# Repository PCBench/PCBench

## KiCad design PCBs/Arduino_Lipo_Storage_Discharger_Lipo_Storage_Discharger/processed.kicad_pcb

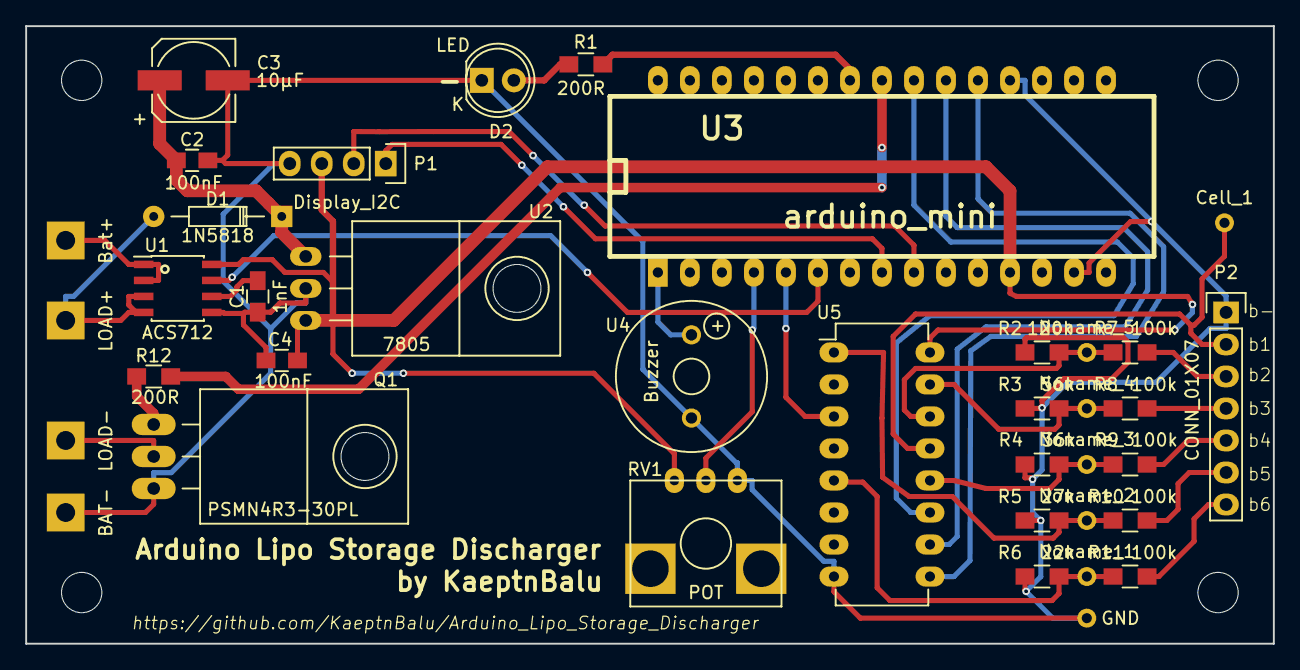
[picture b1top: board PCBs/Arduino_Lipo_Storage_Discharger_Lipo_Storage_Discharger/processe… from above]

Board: 2 copper layers, 99.0 x 49.0 mm, 38 parts (0 on the bottom side), 31 nets.

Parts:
C1: 1nF; C_0805_HandSoldering
C2, C4: 100nF; C_0805_HandSoldering
C3: 10µF; c_elec_6.3x5.3
Cell_1: T1; Measurement_Point_Round-TH_Small
D1: 1N5818; Diode_DO-35_SOD27_Horizontal_RM10
D2: LED; LED-5MM
Noname_1, Noname_2, Noname_3, Noname_4, Noname_5: Measurement_Point_Round-TH_Small
P1: Display_I2C; Socket_Strip_Straight_1x04
P2: CONN_01X07; Pin_Header_Straight_1x07
Q1: PSMN4R3-30PL; TO-220_Neutral123_Horizontal_LargePads
R1, R12: 200R; R_0805_HandSoldering
R2: 120k; R_0805_HandSoldering
R3: 56k; R_0805_HandSoldering
R4: 36k; R_0805_HandSoldering
R5: 27k; R_0805_HandSoldering
R6: 22k; R_0805_HandSoldering
R7, R8, R9, R10, R11: 100k; R_0805_HandSoldering
RV1: POT; RK09K1130A5R
U1: ACS712; SOIC-8_3.9x4.9mm_Pitch1.27mm
U2: 7805; TO-220_7805_Horizontal
U3: arduino_mini
U4: Buzzer; Buzzer_12x8.2_RM6.6
U5: 4051; DIP-16_W7.62mm_LongPads
W1: LOAD+; Measurement_Point_Square-TH_Big
W2: Bat+; Measurement_Point_Square-TH_Big
W3: LOAD-; Measurement_Point_Square-TH_Big
W4: BAT-; Measurement_Point_Square-TH_Big
W5: GND; Measurement_Point_Round-TH_Small

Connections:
/Cell_1: Cell_1.1, P2.2, U5.13
/Cell_2: Noname_5.1, R2.1, R7.2, U5.14
/Cell_3: Noname_4.1, R3.1, R8.2, U5.15
/Cell_4: Noname_3.1, R4.1, R9.2, U5.12
/Cell_5: Noname_2.1, R5.1, R10.2, U5.1
/Cell_6: Noname_1.1, R6.1, R11.2, U5.5
A1: U3.5, U5.3
A2: U1.7, U3.6
Bat+: U1.1, U1.2, W2.1
Bat-: C1.1, C2.2, C3.2, C4.2, D2.1, P1.4, P2.1, Q1.3, R2.2, R3.2, R4.2, R5.2, R6.2, RV1.1, U1.5, U2.GND, U3.14, U3.19, U4.2, U5.8, W4.1, W5.1
D2: U3.20, U5.9
D3: U3.21, U5.10
D4: U3.22, U5.11
D6: R1.2, U3.24
D13: U3.1, U4.1
Input+: D1.2, U1.3, U1.4, W1.1
LOAD-: Q1.2, W3.1
unnamed: C1.2, U1.6
unnamed: C2.1, C3.1, D1.1, U2.VI
unnamed: D2.2, R1.1
unnamed: P2.3, R7.1
unnamed: P2.4, R8.1
unnamed: P2.5, R9.1
unnamed: P2.6, R10.1
unnamed: P2.7, R11.1
unnamed: Q1.1, R12.2
unnamed: R12.1, U3.23
unnamed: RV1.2, U3.4
SCL: P1.2, U3.9
SDA: P1.1, U3.8
VCC: C4.1, P1.3, RV1.3, U1.8, U2.VO, U3.12, U5.16

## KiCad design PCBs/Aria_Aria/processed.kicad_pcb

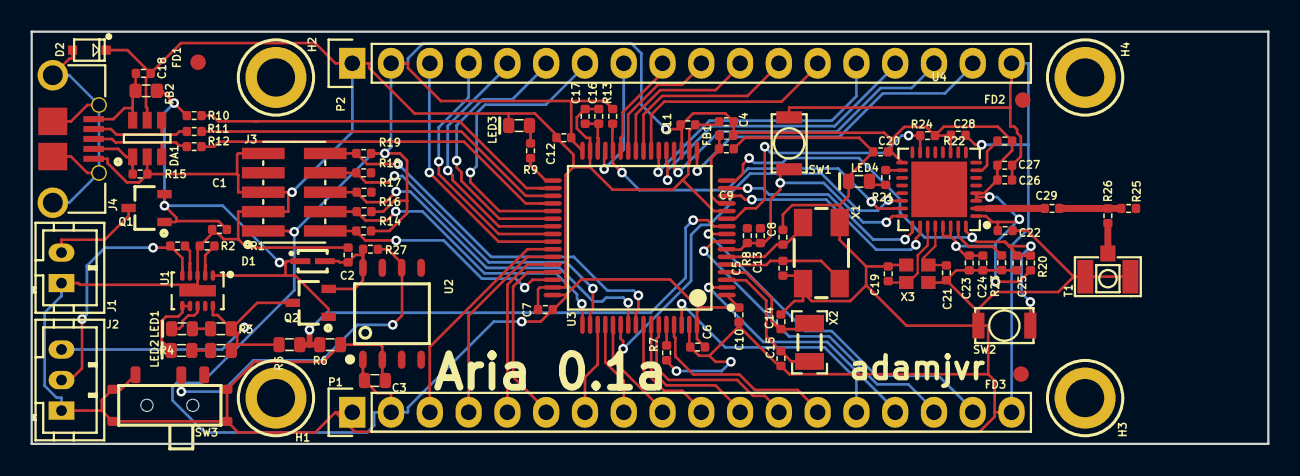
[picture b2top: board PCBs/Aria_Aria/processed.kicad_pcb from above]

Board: 4 copper layers, 81.0 x 27.0 mm, 91 parts (0 on the bottom side), 83 nets.

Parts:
C1, C2: CL05A105KA5NQNC; C0402
C3: CL10A106KQ8NNNC; C0603
C4, C6, C7, C9, C10, C11, C12, C13, C17, C18, C20, C22, C23, C24, C25, C26, C27, C28: CL05B104JP5NNNC; C0402
C5, C8, C19, C21: CL05C090CB5NNNC; C0402
C14, C15: CL05C180GB5NCNC; C0402
C16: CL05A475KQ5NRNC; C0402
C29: 600L5R6BT200T; C0402
D1: BAT20JFILM
D2: RSB39VTE-17
DA1: ESDA6V1BC6
FB1: BLM15HG601SN1D
FB2: MI0603K300R-10
FD1, FD2, FD3: FIDUCIAL
H1, H2, H3, H4: M2.5_Hole; M2.5_HOLE
J1: B2B-PH-K-S(LF)(SN)
J2: B3B-PH-K-S(LF)(SN)
J3: 20021121-00010C4LF
J4: 0475890001-MicroUSBPort; 0475890001
LED1: LTST-C191KGKT; LED0603
LED2: LTST-C191KFKT; LED0603
LED3, LED4: LTST-C193TBKT-5A; LED0603
P1, P2: CONN_01X18; Socket_Strip_Straight_1x18
Q1, Q2: DMG2307L-7
R1: RC1005F4870CS; R0402
R2, R8, R9, R14, R16, R17, R18, R19, R20, R21: RC1005F102CS; R0402
R3, R4: RC1608J202CS; R0603
R5, R6: ERA-3AEB3741V; R0603
R7, R10, R13, R24, R27: RC1005F103CS; R0402
R11, R12: CPF0402B22RE1; R0402
R15: RC1005J473CS; R0402
R22, R23: RC1005F123CS; R0402
R25, R26: ERJ-2GE0R00X; R0402
SW1, SW2: B3U-1000P
SW3: CUS-12TB
T1: 1909763-1
U1: BQ24210DQCT; BQ24210
U2: TC1265-3.3VOA
U3: STM32F446RET6_-_TQFP64; STM32F446RET6
U4: ESP8285
X1: ABM3B8.000MHZB2T
X2: ABS07-32.768KHZ-9-T
X3: FA-128_26.0000MF10Z-AC3

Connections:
+3V3: C3.1, C4.1, C6.1, C7.1, C10.1, C11.1, C12.1, C20.1, C22.1, C23.1, C24.1, C26.1, C27.1, C28.1, FB1.1, J3.1, P1.2, P2.2, R13.1, R14.1, R16.1, R19.1, R20.2, R22.2, R24.1, U2.1, U3.1, U3.19, U3.32, U3.48, U3.64, U4.1, U4.3, U4.4, U4.11, U4.17, U4.29, U4.30
/MCU_STM32F446RET6/BAT_VOLT: R5.2, R6.1, U3.10
/MCU_STM32F446RET6/ESPTOST_BOOT0: U3.54, U4.22
/MCU_STM32F446RET6/ESPTOST_BOOT1: R13.2, U3.28, U4.23
/MCU_STM32F446RET6/ESP_PGM_MODE: R24.2, U3.11, U4.15
/MCU_STM32F446RET6/ESP_ST_RST: C13.1, R8.2, SW1.1, U3.7, U4.24
/MCU_STM32F446RET6/ESP_URX: U3.14, U4.26
/MCU_STM32F446RET6/ESP_UTX: U3.15, U4.25
/MCU_STM32F446RET6/HEARTBEAT: R9.1, U3.33
/MCU_STM32F446RET6/NJTRST: J3.10, R19.2, U3.56
/MCU_STM32F446RET6/PA3: P2.17, U3.17
/MCU_STM32F446RET6/PA4: P2.16, U3.20
/MCU_STM32F446RET6/PA5: P2.15, U3.21
/MCU_STM32F446RET6/PA6: P2.14, U3.22
/MCU_STM32F446RET6/PA7: P2.13, U3.23
/MCU_STM32F446RET6/PA8: P2.3, U3.41
/MCU_STM32F446RET6/PA9: P1.3, U3.42
/MCU_STM32F446RET6/PA10: P1.4, U3.43
/MCU_STM32F446RET6/PA11: P1.5, U3.44
/MCU_STM32F446RET6/PA12: P1.6, U3.45
/MCU_STM32F446RET6/PB0: P2.10, U3.26
/MCU_STM32F446RET6/PB1: P2.9, U3.27
/MCU_STM32F446RET6/PB5: P1.10, U3.57
/MCU_STM32F446RET6/PB6: P1.11, U3.58
/MCU_STM32F446RET6/PB7: P1.12, U3.59
/MCU_STM32F446RET6/PB8: P1.13, U3.61
/MCU_STM32F446RET6/PB9: P1.14, U3.62
/MCU_STM32F446RET6/PB10: P2.8, U3.29
/MCU_STM32F446RET6/PC0: P1.16, U3.8
/MCU_STM32F446RET6/PC1: P1.17, U3.9
/MCU_STM32F446RET6/PC4: P2.12, U3.24
/MCU_STM32F446RET6/PC5: P2.11, U3.25
/MCU_STM32F446RET6/PC6: P2.7, U3.37
/MCU_STM32F446RET6/PC7: P2.6, U3.38
/MCU_STM32F446RET6/PC8: P2.5, U3.39
/MCU_STM32F446RET6/PC9: P2.4, U3.40
/MCU_STM32F446RET6/PC10: P1.7, U3.51
/MCU_STM32F446RET6/PC11: P1.8, U3.52
/MCU_STM32F446RET6/PC12: P1.9, U3.53
/MCU_STM32F446RET6/PC13: P1.15, U3.2
/MCU_STM32F446RET6/STM_ESP_RST: C25.1, R20.1, SW2.2, U3.16, U4.32
/MCU_STM32F446RET6/SWCLK_TCK: J3.4, R16.2, U3.49
/MCU_STM32F446RET6/SWDIO_TMS: J3.2, R14.2, U3.46
/MCU_STM32F446RET6/SWO_TDI: J3.8, R18.2, U3.50
/MCU_STM32F446RET6/SWO_TDO: J3.6, R17.2, U3.55
/MCU_STM32F446RET6/VBUS: C1.1, D1.1, FB2.1, Q1.1, Q1.2, Q2.1, R10.2, U1.1
/Power/BAT: J2.3, Q2.3, R3.2, R4.2, R5.1, U1.10
/Power/LDO_VIN: C2.1, D1.2, Q2.2, R27.1, U2.8
/Power/THERM: J2.2, R2.2, U1.5
/WiFi-ESP8285/ANTENNA: C29.2, R25.1, R26.1
/WiFi-ESP8285/ANT_UM: R26.2, T1.1
/WiFi-ESP8285/LNA: C29.1, U4.2
GND: C1.2, C2.2, C3.2, C4.2, C5.2, C6.2, C7.2, C8.2, C9.2, C10.2, C11.2, C12.2, C14.2, C15.2, C16.2, C17.2, C18.1, C19.2, C20.2, C21.2, C22.2, C23.2, C24.2, C25.2, C26.2, C27.2, C28.2, D2.2, DA1.2, DA1.5, J1.1, J2.1, J3.3, J3.5, J3.9, J4.5, LED3.2, LED4.2, P1.1, P1.18, P2.1, P2.18, R1.2, R6.2, R7.2, R15.2, R23.1, SW1.2, SW2.1, SW3.1, SW3.4, T1.2, U1.3, U1.11, U2.2, U3.12, U3.18, U3.31, U3.47, U3.63, X1.2, X1.4, X3.2, X3.4
unnamed: C5.1, U3.5, X1.1
unnamed: C8.1, U3.6, X1.3
unnamed: C9.1, FB1.2, U3.13
unnamed: C14.1, U3.4, X2.1
unnamed: C15.1, U3.3, X2.2
unnamed: C16.1, C17.1, U3.30
unnamed: C18.2, DA1.6, FB2.2, J4.1
unnamed: C19.1, U4.27, X3.1
unnamed: C21.1, U4.28, X3.3
unnamed: D2.1, J4.6, J4.7, J4.8, J4.9, J4.10, J4.11
unnamed: DA1.1, J4.4, R15.1
unnamed: DA1.3, J4.3, R12.2
unnamed: DA1.4, J4.2, R11.2
unnamed: J1.2, Q1.3
unnamed: LED1.1, R3.1
unnamed: LED1.2, U1.8
unnamed: LED2.1, R4.1
unnamed: LED2.2, U1.6, U1.7
unnamed: LED3.1, R9.2
unnamed: LED4.1, R21.2
unnamed: R1.1, U1.2
unnamed: R2.1, U1.4
unnamed: R7.1, U3.60
unnamed: R10.1, U3.34
unnamed: R11.1, U3.35
unnamed: R12.1, U3.36
unnamed: R21.1, U4.18
unnamed: R22.1, U4.7
unnamed: R23.2, U4.31
unnamed: R27.2, SW3.2, U2.6

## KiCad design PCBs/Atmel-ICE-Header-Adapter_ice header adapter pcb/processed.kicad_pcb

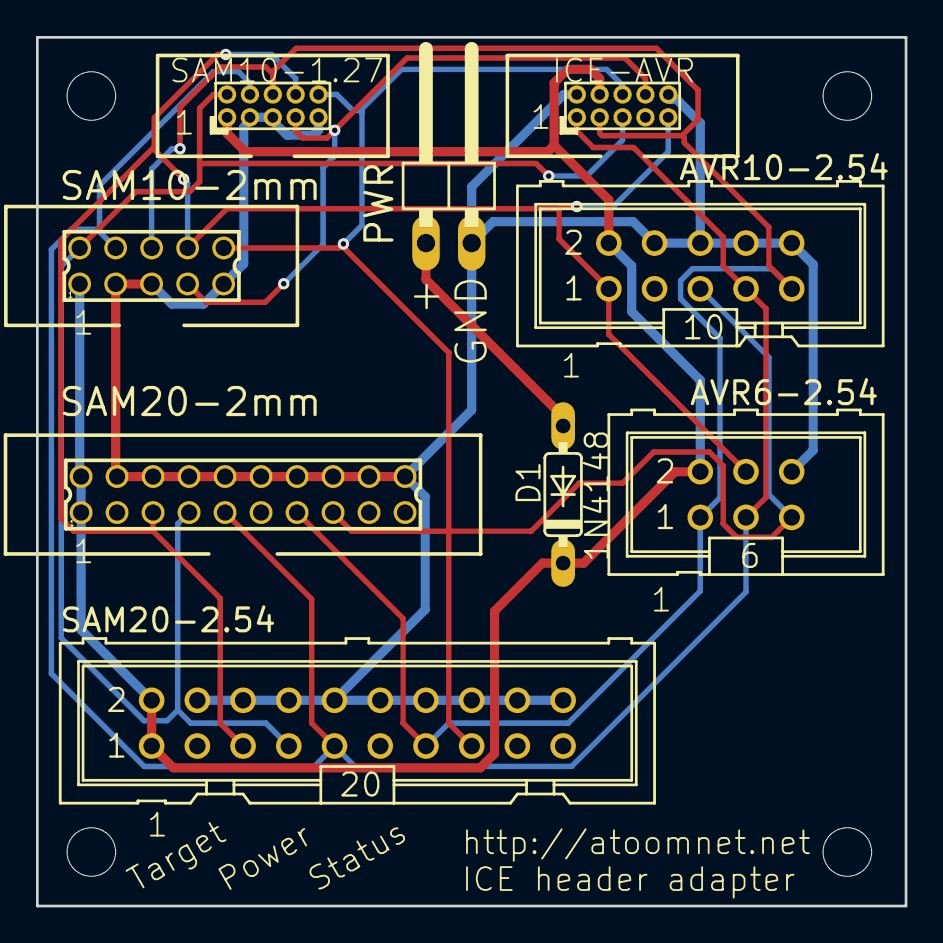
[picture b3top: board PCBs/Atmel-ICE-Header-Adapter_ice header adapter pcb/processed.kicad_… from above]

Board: 2 copper layers, 48.3 x 48.3 mm, 13 parts (0 on the bottom side), 9 nets.

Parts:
AVR6-2.54: ML6
AVR10-2.54: ML10
D1: 1N4148; DO35-7
ICE-AVR1: PINHEAD_PINHD-2X5; PINHEAD_2X05_127
P1, P2, P3, P4: TST; MountingHole_2.7mm_M2.5
PWR1: PINHD-1X2; 1X02_90
SAM10-1.27: PINHEAD_PINHD-2X5; PINHEAD_2X05_127
SAM10-2: 87758-1016
SAM20-2: 87758-2016
SAM20-2.54: ML20

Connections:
/GND: AVR6-2.54.6, AVR10-2.54.4, AVR10-2.54.6, AVR10-2.54.8, AVR10-2.54.10, ICE-AVR1.2, ICE-AVR1.10, PWR1.2, SAM10-1.27.3, SAM10-1.27.5, SAM10-1.27.9, SAM10-2.3, SAM10-2.5, SAM10-2.9, SAM20-2.4, SAM20-2.6, SAM20-2.8, SAM20-2.10, SAM20-2.12, SAM20-2.14, SAM20-2.16, SAM20-2.18, SAM20-2.20, SAM20-2.54.4, SAM20-2.54.6, SAM20-2.54.8, SAM20-2.54.10, SAM20-2.54.12, SAM20-2.54.14, SAM20-2.54.16, SAM20-2.54.18, SAM20-2.54.20
/NSRST: AVR6-2.54.5, AVR10-2.54.5, ICE-AVR1.6, SAM10-1.27.10, SAM10-2.10, SAM20-2.15, SAM20-2.54.15
/NTRST: ICE-AVR1.8, SAM10-1.27.7, SAM10-2.7
/TCK: AVR6-2.54.3, AVR10-2.54.7, ICE-AVR1.1, SAM10-1.27.4, SAM10-2.4, SAM20-2.9, SAM20-2.54.9
/TDI: AVR6-2.54.4, AVR10-2.54.1, ICE-AVR1.9, SAM10-1.27.8, SAM10-2.8, SAM20-2.5, SAM20-2.54.5
/TDO: AVR6-2.54.1, AVR10-2.54.9, ICE-AVR1.3, SAM10-1.27.6, SAM10-2.6, SAM20-2.13, SAM20-2.54.13
/TMS: ICE-AVR1.5, SAM10-1.27.2, SAM10-2.2, SAM20-2.7, SAM20-2.54.7
/VTG: AVR6-2.54.2, AVR10-2.54.2, D1.C, ICE-AVR1.4, SAM10-1.27.1, SAM10-2.1, SAM20-2.1, SAM20-2.2, SAM20-2.54.1, SAM20-2.54.2
unnamed: D1.A, PWR1.1

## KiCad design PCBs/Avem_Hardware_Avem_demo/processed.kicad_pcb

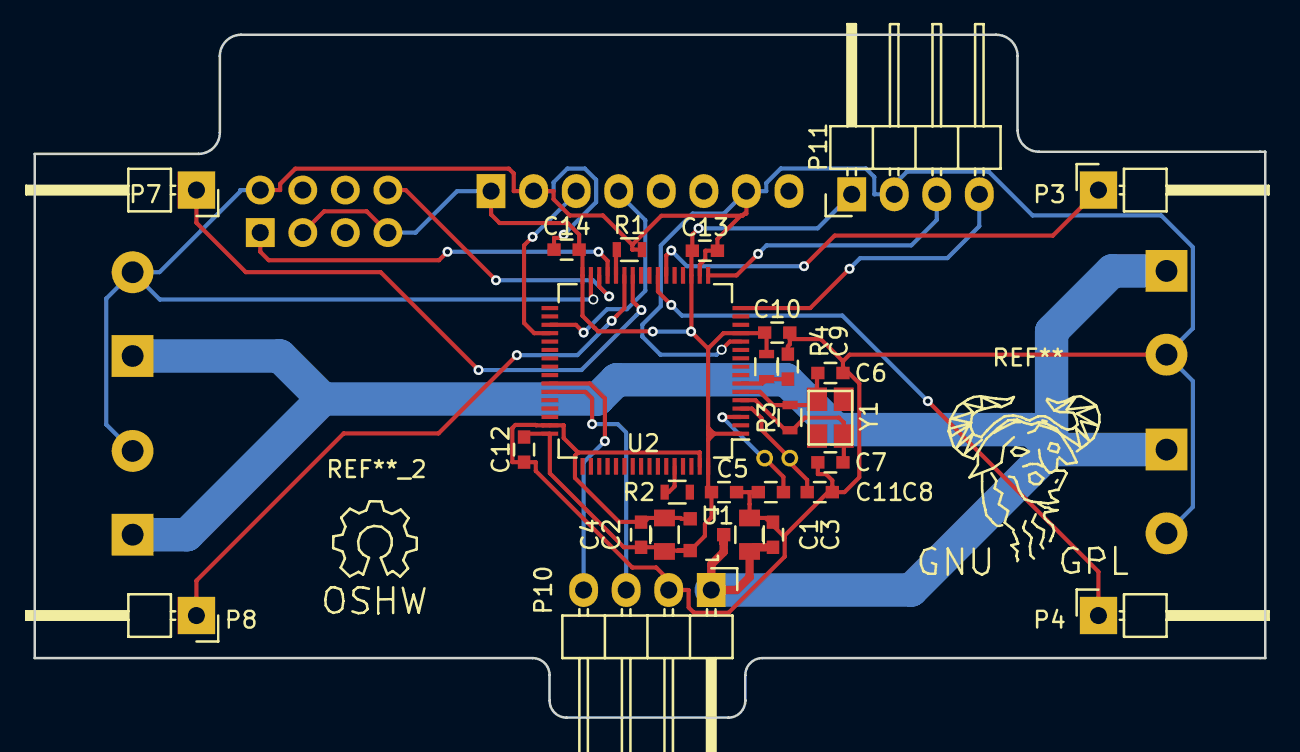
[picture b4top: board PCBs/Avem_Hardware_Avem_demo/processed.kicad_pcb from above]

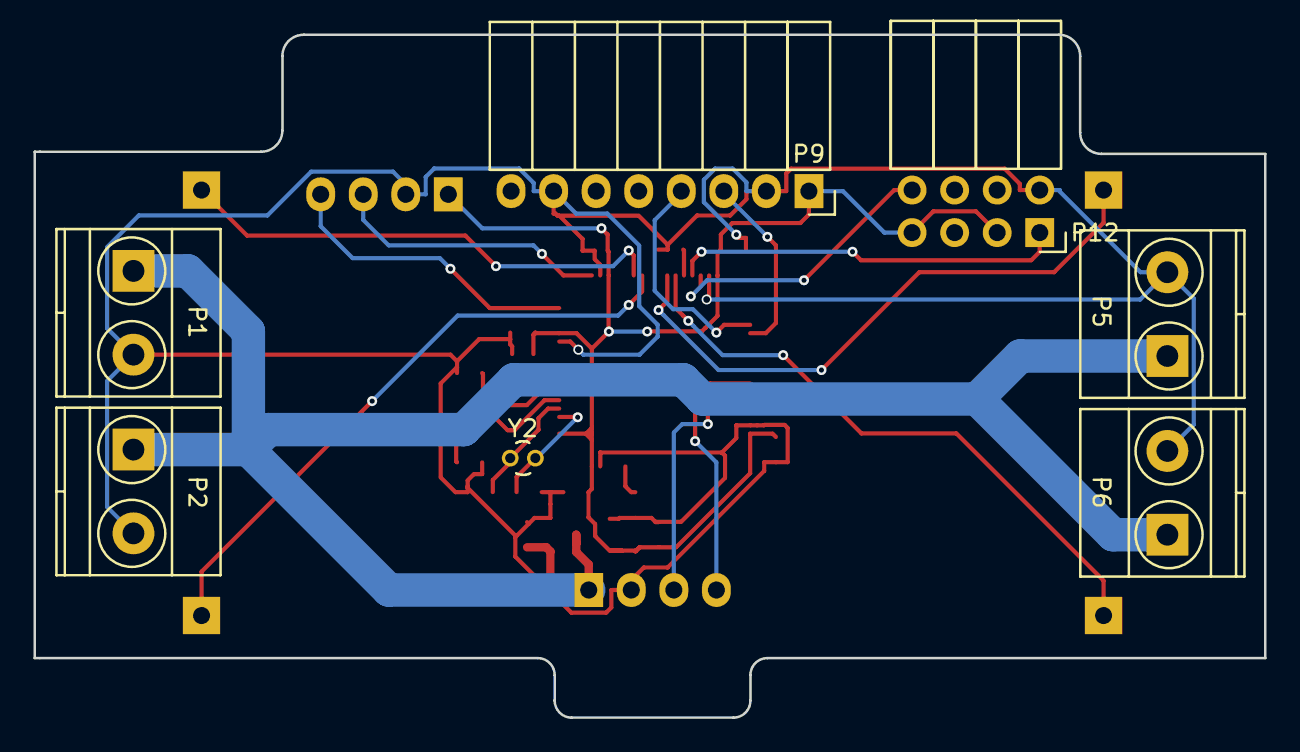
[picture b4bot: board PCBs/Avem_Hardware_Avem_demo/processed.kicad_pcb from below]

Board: 2 copper layers, 73.5 x 40.8 mm, 34 parts (7 on the bottom side), 22 nets.

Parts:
C1, C2: C_0805
C3, C4, C5, C6, C7, C8, C9, C10, C11, C12, C13, C14: C_0603
P1, P2, P5, P6: TerminalBlock_Pheonix_MKDS1.5-2pol
P3, P4, P7, P8: Pin_Header_Angled_1x01
P9: Socket_Strip_Angled_1x08
P10: ISP; Pin_Header_Angled_1x04
P11: Pin_Header_Angled_1x04
P12: Socket_Strip_Angled_2x04
R1, R2, R3, R4: R_0603
U1: SOT-23
U2: STM32F103RCT6; LQFP-64_10x10mm_Pitch0.5mm
Y1: crystal_FA238-TSX3225
Y2: Crystal_Round_Vertical_2mm

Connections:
3V3: C2.1, C4.2, C5.1, C10.1, C12.1, C13.1, C14.1, P9.1, P11.1, P12.3, P12.7, R4.1, U1.2, U2.1, U2.13, U2.19, U2.32, U2.48, U2.64
+3V3: C1.1, C3.2, P1.1, P2.1, P5.1, P6.1, P10.1, U1.3
BLDC1: P3.1, U2.22
BLDC2: P4.1, U2.23
BLDC3: P7.1, U2.26
BLDC4: P8.1, U2.27
BOOT0: R2.2, U2.60
BOOT1: R1.2, U2.28
GND: C1.2, C2.2, C3.1, C4.1, C5.2, C6.2, C7.2, C8.2, C9.2, C10.2, C11.2, C12.2, C13.2, C14.2, P1.2, P2.2, P5.2, P6.2, P9.2, P9.7, P10.2, P11.2, P12.2, R1.1, U1.1, U2.12, U2.18, U2.31, U2.47, U2.63
OSCIN: C7.1, R3.2, U2.5, Y1.2
OSCIN32: C11.1, U2.3, Y2.2
OSCOUT: C6.1, R3.1, U2.6, Y1.1
OSCOUT32: C8.1, U2.4, Y2.1
RESET: C9.1, R4.2, U2.7
RX1: P10.3, U2.43
RX2: P11.3, U2.17
RX3: P12.8, U2.30
SCL: P9.3, U2.36
SDA: P9.4, U2.35
TX1: P10.4, U2.42
TX2: P11.4, U2.16
TX3: P12.1, U2.29

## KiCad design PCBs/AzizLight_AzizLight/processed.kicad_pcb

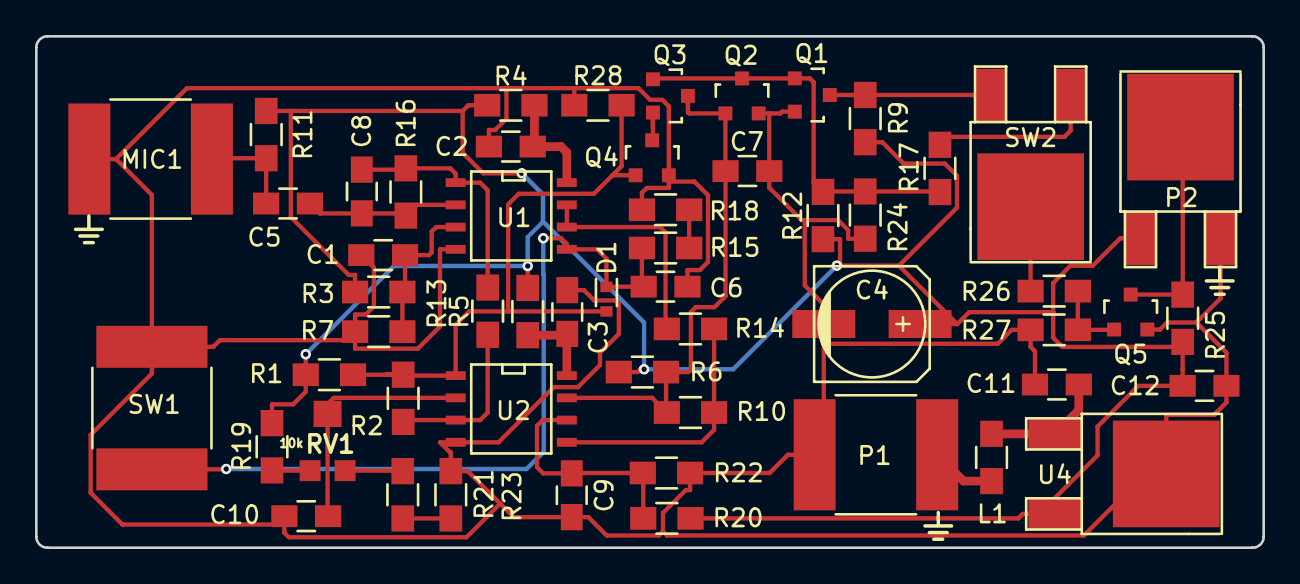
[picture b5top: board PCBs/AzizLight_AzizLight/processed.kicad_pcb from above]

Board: 2 copper layers, 70.1 x 29.2 mm, 55 parts (0 on the bottom side), 29 nets.

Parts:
C1, C2, C3, C5, C9, C10, C12: 0.1uF; C_0805_HandSoldering
C4: 100uF; c_elec_6.3x5.8
C6, C7: 10uF; C_0805_HandSoldering
C8: 100pF; C_0805_HandSoldering
C11: 0.33uF; C_0805_HandSoldering
D1: 1N4148; SOD-523
L1: 10uH; R_0805_HandSoldering
MIC1: POM-3535; C_2225_HandSoldering
P1: +9V; C_2225_HandSoldering
P2: Trigger Out; TO-252-2Lead
Q1, Q2, Q3, Q4, Q5: BS170; SOT-23
R1, R3, R7, R13, R19, R21, R22, R23: 10k; R_0805_HandSoldering
R2: 220k; R_0805_HandSoldering
R4, R5, R17, R26: 100; R_0805_HandSoldering
R6: 100k; R_0805_HandSoldering
R9, R12, R25: 4.7k; R_0805_HandSoldering
R10: 470k; R_0805_HandSoldering
R11: 5.6k; R_0805_HandSoldering
R14: 120k; R_0805_HandSoldering
R15, R18: 10M; R_0805_HandSoldering
R16: 560k; R_0805_HandSoldering
R20: 12k; R_0805_HandSoldering
R24, R27, R28: 1M; R_0805_HandSoldering
RV1: 10k; TRIMPOT_SMD
SW1: Reset; C_2225_HandSoldering
SW2: Invert; TO-252-2Lead
U1: MCP602; SOIC-8-N
U2: LM393; SOIC-8-N
U4: MC7805; TO-252-2Lead

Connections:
+5V: C4.1, C12.1, P2.1, R1.2, R3.1, R4.1, R5.1, R6.1, R9.1, R11.1, R12.1, R19.2, R20.1, R25.1, U4.3
GND: C1.2, C2.1, C3.1, C4.2, C6.2, C7.2, C9.2, C10.2, C11.2, C12.2, MIC1.2, P1.1, P2.3, Q1.2, Q2.2, Q4.2, Q5.2, R7.2, R18.1, R22.1, R23.1, R24.1, R27.1, R28.1, SW1.1, U1.4, U2.4, U4.2
unnamed: C1.1, R3.2, R7.1, U1.3
unnamed: C2.2, R4.2, U1.8
unnamed: C3.2, R5.2, U2.8
unnamed: C5.1, C8.2, R16.2, U1.2
unnamed: C5.2, MIC1.1, R11.2
unnamed: C6.1, D1.1, R15.2, SW1.2, U1.5
unnamed: C7.1, Q2.1, Q3.3, R6.2, R10.1, U2.7
unnamed: C8.1, R13.2, R16.1, U1.1
unnamed: C9.1, R20.2, R22.2, U2.6
unnamed: C10.1, RV1.2, U2.2
unnamed: C11.1, L1.2, U4.1
unnamed: D1.2, Q4.1, R1.1, R2.1, R28.2, U2.1
unnamed: L1.1, P1.2
unnamed: P2.2, Q5.3, R25.2
unnamed: Q1.1, Q2.3, Q3.1, R12.2, R17.2, R24.2
unnamed: Q1.3, R9.2, SW2.3
unnamed: Q3.2, Q4.3
unnamed: Q5.1, R26.1, R27.2
unnamed: R10.2, R14.1, U2.5
unnamed: R2.2, R13.1, U2.3
unnamed: R14.2, U1.6, U1.7
unnamed: R15.1, R18.2
unnamed: R17.1, SW2.1
unnamed: R19.1, RV1.1
unnamed: R21.1, R23.2
unnamed: R21.2, RV1.3
unnamed: R26.2, SW2.2
